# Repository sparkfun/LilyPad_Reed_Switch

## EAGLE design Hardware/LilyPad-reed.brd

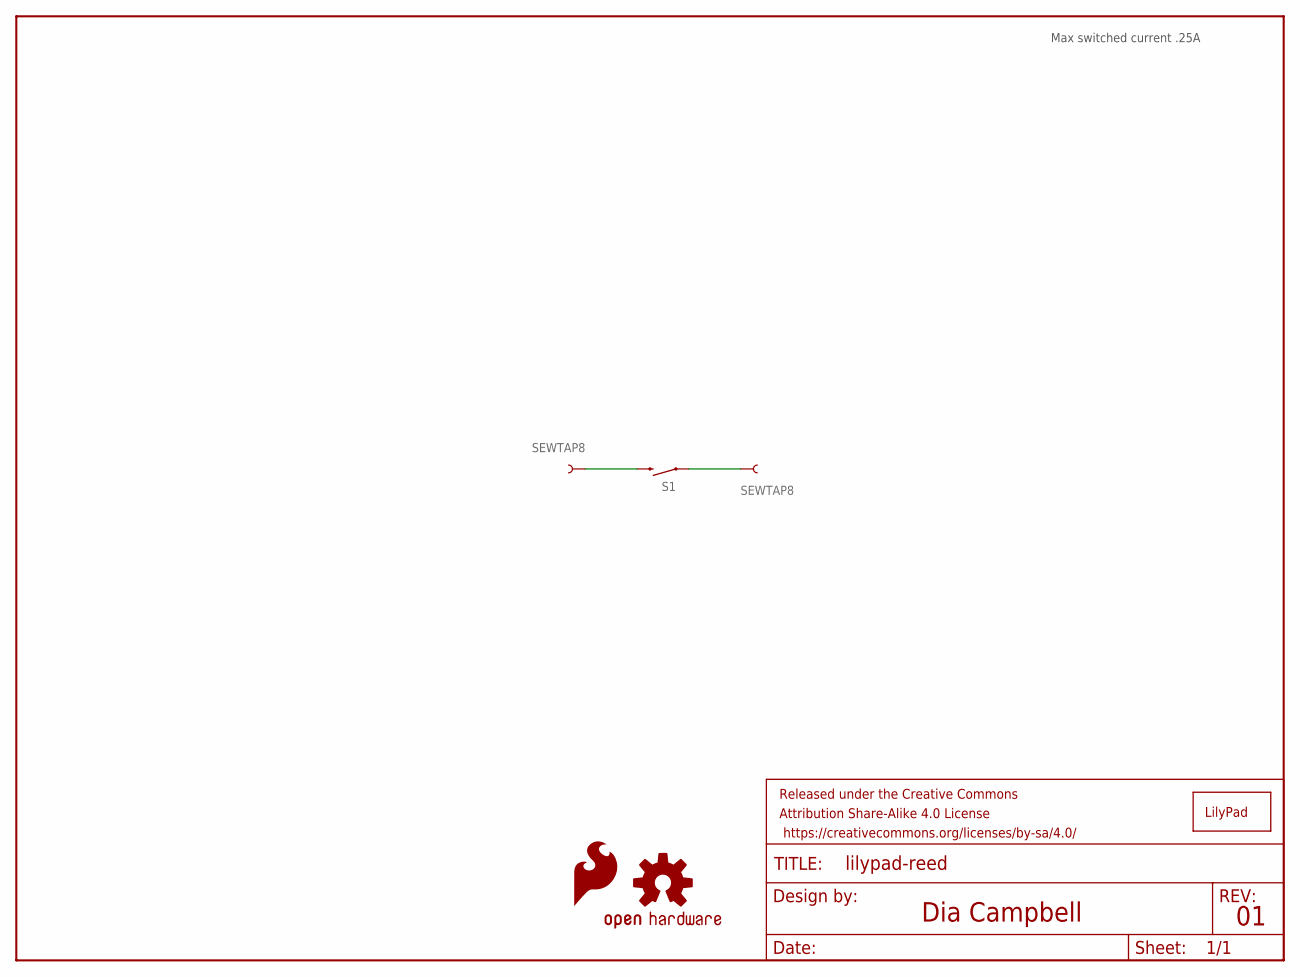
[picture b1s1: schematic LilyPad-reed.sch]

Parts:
FRAME1: FRAME-LETTER; CREATIVE_COMMONS
LOGO1: OSHW-LOGOS-COPPER; OSHW-LOGO-S_COPPER
LOGO2: SFE_LOGO_FLAME.1COP; SFE_LOGO_FLAME_COPPER_.1
S1: REED; REED_SWITCH_PLASTIC
SLIDEOFF: SEWTAP8; PETAL-MEDIUM-2SIDE
SLIDEON: SEWTAP8; PETAL-MEDIUM-2SIDE
U$1: LOGO-LPLP; LOGO-LILYPAD

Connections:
unnamed: S1.P$2 (2), SLIDEOFF.1
unnamed: S1.P$1 (1), SLIDEON.1

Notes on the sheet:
Dia Campbell
Max switched current .25A

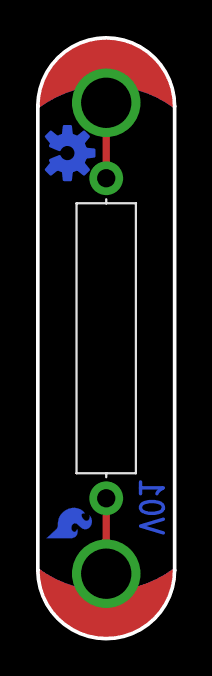
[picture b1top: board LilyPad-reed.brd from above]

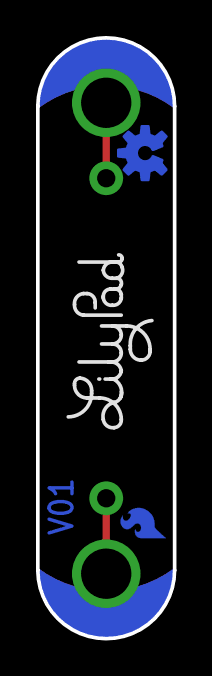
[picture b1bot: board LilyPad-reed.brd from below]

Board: 2 copper layers, 7.6 x 33.4 mm, 7 parts (3 on the bottom side), 2 nets.

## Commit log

2015-03-02 Initial commit -ready for 1st review
2015-03-02 updating to SFE .gitignore
2015-03-09 post-review edits
    added PTH pins
2015-04-02 Increased trace width, added dimension
2015-04-02 Adding ProdID to reed switch
2015-04-06 Updated copper flame
2015-04-07 QC checklist changes
2015-05-19 Fixed version number for redboards
2015-07-30 created panel v10
2015-11-05 adding license and readme

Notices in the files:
parts and their libraries:
SparkFun-Electromechanical: Licensing: Creative Commons ShareAlike 4.0 International - https://creativecommons.org/licenses/by-sa/4.0
SparkFun-Aesthetics: Released under the Creative Commons Attribution Share-Alike 4.0 License
SparkFun-Aesthetics: https://creativecommons.org/licenses/by-sa/4.0
